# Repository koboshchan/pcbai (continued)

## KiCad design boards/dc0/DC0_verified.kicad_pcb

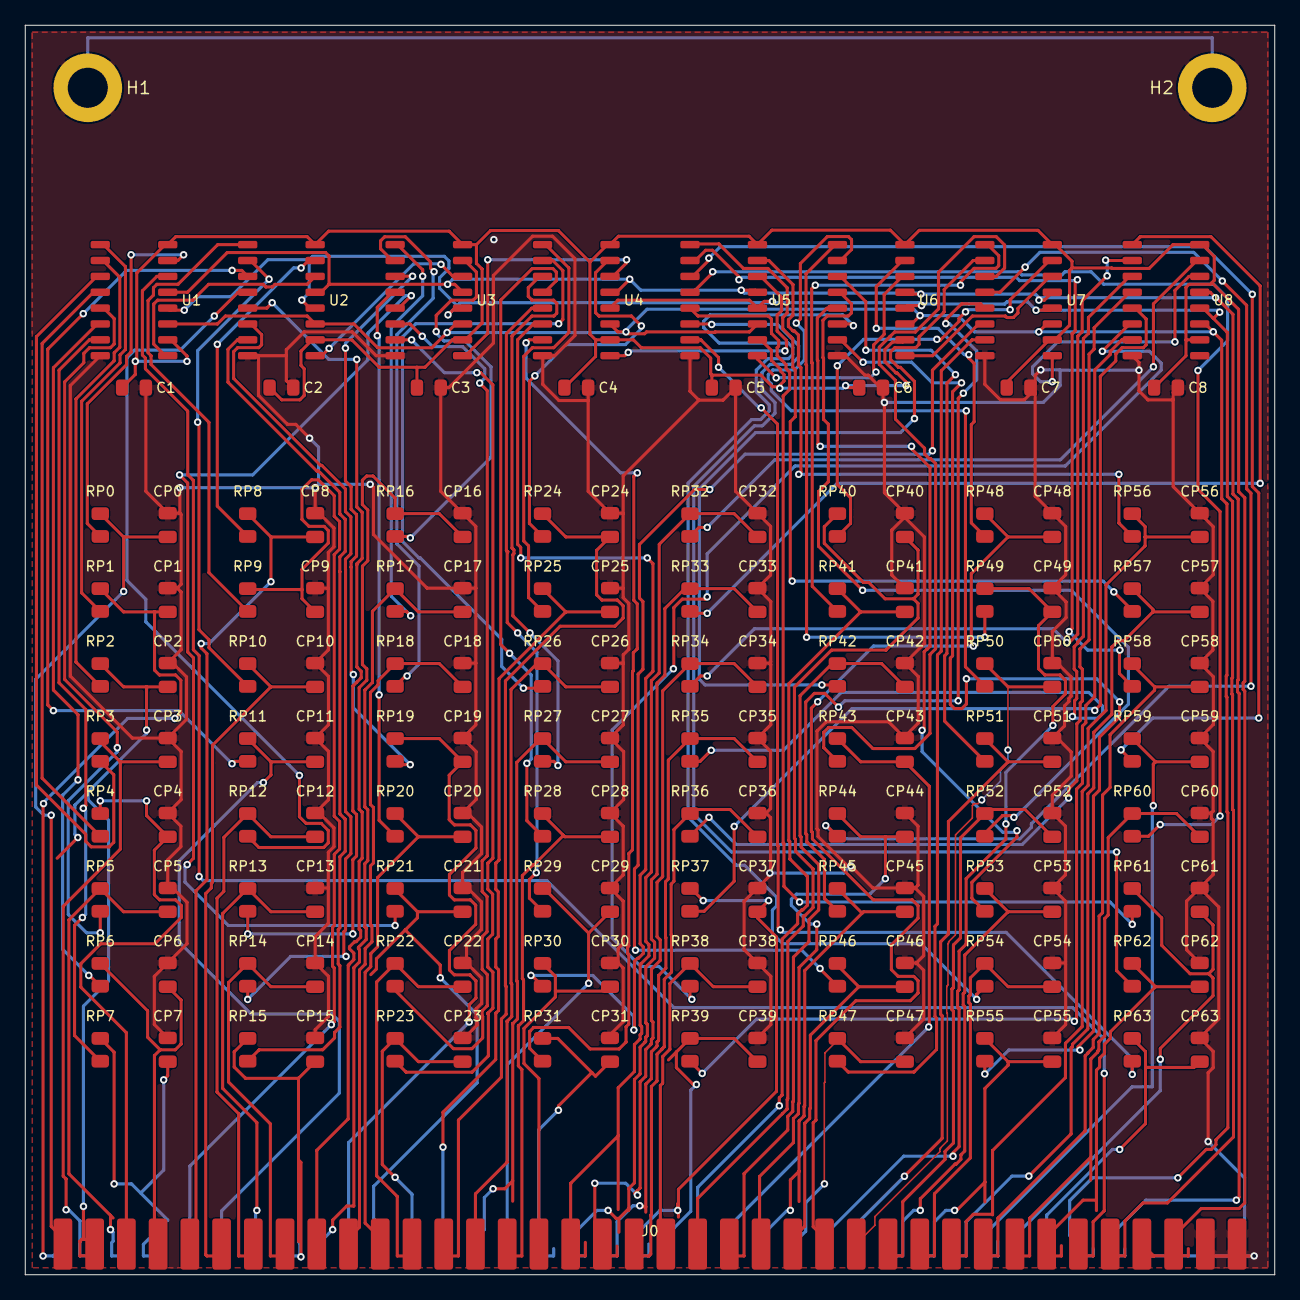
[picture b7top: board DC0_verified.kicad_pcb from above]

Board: 2 copper layers, 100.0 x 100.0 mm, 147 parts (0 on the bottom side), 141 nets.

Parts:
C1, C2, C3, C4, C5, C6, C7, C8: 0.1uF; C_0805_2012Metric
CP0, CP1, CP2, CP3, CP4, CP5, CP6, CP7, CP8, CP9, CP10, CP11, CP12, CP13, CP14, CP15, CP16, CP17, CP18, CP19, CP20, CP21, CP22, CP23, CP24, CP25, CP26, CP27, CP28, CP29, CP30, CP31, CP32, CP33, CP34, CP35, CP36, CP37, CP38, CP39, CP40, CP41, CP42, CP43, CP44, CP45, CP46, CP47, CP48, CP49, CP50, CP51, CP52, CP53, CP54, CP55, CP56, CP57, CP58, CP59, CP60, CP61, CP62, CP63: 1uF; C_0805_2012Metric
H1, H2: MountingHole; MountingHole_3.2mm_M3_Pad
J0: 2x38_2.54mm_GENERIC_MANUAL_STRADDLE; Straddle2x38
RP0, RP1, RP2, RP3, RP4, RP5, RP6, RP7, RP8, RP9, RP10, RP11, RP12, RP13, RP14, RP15, RP16, RP17, RP18, RP19, RP20, RP21, RP22, RP23, RP24, RP25, RP26, RP27, RP28, RP29, RP30, RP31, RP32, RP33, RP34, RP35, RP36, RP37, RP38, RP39, RP40, RP41, RP42, RP43, RP44, RP45, RP46, RP47, RP48, RP49, RP50, RP51, RP52, RP53, RP54, RP55, RP56, RP57, RP58, RP59, RP60, RP61, RP62, RP63: 10k; R_0805_2012Metric
U1, U2, U3, U4, U5, U6, U7, U8: 74AHCT595S16-13; SOIC-16_3.9x9.9mm_P1.27mm

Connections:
+5V: C1.1, C2.1, C3.1, C4.1, C5.1, C6.1, C7.1, C8.1, J0.69, J0.71, U1.10, U1.16, U2.10, U2.16, U3.10, U3.16, U4.10, U4.16, U5.10, U5.16, U6.10, U6.16, U7.10, U7.16, U8.10, U8.16
GND: C1.2, C2.2, C3.2, C4.2, C5.2, C6.2, C7.2, C8.2, CP0.2, CP1.2, CP2.2, CP3.2, CP4.2, CP5.2, CP6.2, CP7.2, CP8.2, CP9.2, CP10.2, CP11.2, CP12.2, CP13.2, CP14.2, CP15.2, CP16.2, CP17.2, CP18.2, CP19.2, CP20.2, CP21.2, CP22.2, CP23.2, CP24.2, CP25.2, CP26.2, CP27.2, CP28.2, CP29.2, CP30.2, CP31.2, CP32.2, CP33.2, CP34.2, CP35.2, CP36.2, CP37.2, CP38.2, CP39.2, CP40.2, CP41.2, CP42.2, CP43.2, CP44.2, CP45.2, CP46.2, CP47.2, CP48.2, CP49.2, CP50.2, CP51.2, CP52.2, CP53.2, CP54.2, CP55.2, CP56.2, CP57.2, CP58.2, CP59.2, CP60.2, CP61.2, CP62.2, CP63.2, H1.1, H2.1, J0.70, J0.72, J0.73, J0.74, J0.75, J0.76, U1.8, U2.8, U3.8, U4.8, U5.8, U6.8, U7.8, U8.8
IN_0: CP0.1, J0.1, RP0.2
IN_1: CP1.1, J0.2, RP1.2
IN_2: CP2.1, J0.3, RP2.2
IN_3: CP3.1, J0.4, RP3.2
IN_4: CP4.1, J0.5, RP4.2
IN_5: CP5.1, J0.6, RP5.2
IN_6: CP6.1, J0.7, RP6.2
IN_7: CP7.1, J0.8, RP7.2
IN_8: CP8.1, J0.9, RP8.2
IN_9: CP9.1, J0.10, RP9.2
IN_10: CP10.1, J0.11, RP10.2
IN_11: CP11.1, J0.12, RP11.2
IN_12: CP12.1, J0.13, RP12.2
IN_13: CP13.1, J0.14, RP13.2
IN_14: CP14.1, J0.15, RP14.2
IN_15: CP15.1, J0.16, RP15.2
IN_16: CP16.1, J0.17, RP16.2
IN_17: CP17.1, J0.18, RP17.2
IN_18: CP18.1, J0.19, RP18.2
IN_19: CP19.1, J0.20, RP19.2
IN_20: CP20.1, J0.21, RP20.2
IN_21: CP21.1, J0.22, RP21.2
IN_22: CP22.1, J0.23, RP22.2
IN_23: CP23.1, J0.24, RP23.2
IN_24: CP24.1, J0.25, RP24.2
IN_25: CP25.1, J0.26, RP25.2
IN_26: CP26.1, J0.27, RP26.2
IN_27: CP27.1, J0.28, RP27.2
IN_28: CP28.1, J0.29, RP28.2
IN_29: CP29.1, J0.30, RP29.2
IN_30: CP30.1, J0.31, RP30.2
IN_31: CP31.1, J0.32, RP31.2
IN_32: CP32.1, J0.33, RP32.2
IN_33: CP33.1, J0.34, RP33.2
IN_34: CP34.1, J0.35, RP34.2
IN_35: CP35.1, J0.36, RP35.2
IN_36: CP36.1, J0.37, RP36.2
IN_37: CP37.1, J0.38, RP37.2
IN_38: CP38.1, J0.39, RP38.2
IN_39: CP39.1, J0.40, RP39.2
IN_40: CP40.1, J0.41, RP40.2
IN_41: CP41.1, J0.42, RP41.2
IN_42: CP42.1, J0.43, RP42.2
IN_43: CP43.1, J0.44, RP43.2
IN_44: CP44.1, J0.45, RP44.2
IN_45: CP45.1, J0.46, RP45.2
IN_46: CP46.1, J0.47, RP46.2
IN_47: CP47.1, J0.48, RP47.2
IN_48: CP48.1, J0.49, RP48.2
IN_49: CP49.1, J0.50, RP49.2
IN_50: CP50.1, J0.51, RP50.2
IN_51: CP51.1, J0.52, RP51.2
IN_52: CP52.1, J0.53, RP52.2
IN_53: CP53.1, J0.54, RP53.2
IN_54: CP54.1, J0.55, RP54.2
IN_55: CP55.1, J0.56, RP55.2
IN_56: CP56.1, J0.57, RP56.2
IN_57: CP57.1, J0.58, RP57.2
IN_58: CP58.1, J0.59, RP58.2
IN_59: CP59.1, J0.60, RP59.2
IN_60: CP60.1, J0.61, RP60.2
IN_61: CP61.1, J0.62, RP61.2
IN_62: CP62.1, J0.63, RP62.2
IN_63: CP63.1, J0.64, RP63.2
RAW_IN_0: RP0.1, U1.15
RAW_IN_1: RP1.1, U1.1
RAW_IN_2: RP2.1, U1.2
RAW_IN_3: RP3.1, U1.3
RAW_IN_4: RP4.1, U1.4
RAW_IN_5: RP5.1, U1.5
RAW_IN_6: RP6.1, U1.6
RAW_IN_7: RP7.1, U1.7
RAW_IN_8: RP8.1, U2.15
RAW_IN_9: RP9.1, U2.1
RAW_IN_10: RP10.1, U2.2
RAW_IN_11: RP11.1, U2.3
RAW_IN_12: RP12.1, U2.4
RAW_IN_13: RP13.1, U2.5
RAW_IN_14: RP14.1, U2.6
RAW_IN_15: RP15.1, U2.7
RAW_IN_16: RP16.1, U3.15
RAW_IN_17: RP17.1, U3.1
RAW_IN_18: RP18.1, U3.2
RAW_IN_19: RP19.1, U3.3
RAW_IN_20: RP20.1, U3.4
RAW_IN_21: RP21.1, U3.5
RAW_IN_22: RP22.1, U3.6
RAW_IN_23: RP23.1, U3.7
RAW_IN_24: RP24.1, U4.15
RAW_IN_25: RP25.1, U4.1
RAW_IN_26: RP26.1, U4.2
RAW_IN_27: RP27.1, U4.3
RAW_IN_28: RP28.1, U4.4
RAW_IN_29: RP29.1, U4.5
RAW_IN_30: RP30.1, U4.6
RAW_IN_31: RP31.1, U4.7
RAW_IN_32: RP32.1, U8.15
RAW_IN_33: RP33.1, U8.1
RAW_IN_34: RP34.1, U8.2
RAW_IN_35: RP35.1, U8.3
RAW_IN_36: RP36.1, U8.4
RAW_IN_37: RP37.1, U8.5
RAW_IN_38: RP38.1, U8.6
RAW_IN_39: RP39.1, U8.7
RAW_IN_40: RP40.1, U7.15
RAW_IN_41: RP41.1, U7.1
RAW_IN_42: RP42.1, U7.2
RAW_IN_43: RP43.1, U7.3
RAW_IN_44: RP44.1, U7.4
RAW_IN_45: RP45.1, U7.5
RAW_IN_46: RP46.1, U7.6
RAW_IN_47: RP47.1, U7.7
RAW_IN_48: RP48.1, U6.15
RAW_IN_49: RP49.1, U6.1
RAW_IN_50: RP50.1, U6.2
RAW_IN_51: RP51.1, U6.3
RAW_IN_52: RP52.1, U6.4
RAW_IN_53: RP53.1, U6.5
RAW_IN_54: RP54.1, U6.6
RAW_IN_55: RP55.1, U6.7
RAW_IN_56: RP56.1, U5.15
RAW_IN_57: RP57.1, U5.1
RAW_IN_58: RP58.1, U5.2
RAW_IN_59: RP59.1, U5.3
RAW_IN_60: RP60.1, U5.4
RAW_IN_61: RP61.1, U5.5
RAW_IN_62: RP62.1, U5.6
RAW_IN_63: RP63.1, U5.7
SPI_LATCH: J0.67, U1.12, U2.12, U3.12, U4.12, U5.12, U6.12, U7.12, U8.12
SPI_MOSI: J0.65, U1.14
SPI_OE: J0.68, U1.13, U2.13, U3.13, U4.13, U5.13, U6.13, U7.13, U8.13
SPI_SCK: J0.66, U1.11, U2.11, U3.11, U4.11, U5.11, U6.11, U7.11, U8.11
SR_CHAIN_1: U1.9, U2.14
SR_CHAIN_2: U2.9, U3.14
SR_CHAIN_3: U3.9, U4.14
SR_CHAIN_4: U4.9, U5.14
SR_CHAIN_5: U5.9, U6.14
SR_CHAIN_6: U6.9, U7.14
SR_CHAIN_7: U7.9, U8.14

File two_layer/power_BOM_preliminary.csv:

Comment,Designator,Footprint,LCSC Part #
Diodes 74AHCT595S16-13 - approved JLC Extended SMT assembly all8,"U_SR1,U_SR2,U_SR3,U_SR4,U_SR5,U_SR6,U_SR7,U_SR8",SOIC-16_3.9x9.9mm_P1.27mm,C126402
ST L7805CV - manual TH assembly; cooling optional recommended; clock limits require qualification,U_REG5,TO-220-3_Vertical,C111887
1uF 50V X7R +/-10% Samsung CL21B105KBFNNNE - JLC Basic SMT practical input bypass,C_REG_IN,C_0805_2012Metric,C28323
0.1uF 50V X7R - purchasing part pending,C_REG_OUT,C_0805_2012Metric,
10uF >=16V polarized - purchasing part pending,C_REG_BULK,CP_Elec_5x5.8,
0ohm mandatory shared5V reference link - purchasing part pending,R_REF_LINK,R_0805_2012Metric,
820ohm5% >=0.125W minimum load - purchasing part pending,R_REG_MINLOAD,R_0805_2012Metric,

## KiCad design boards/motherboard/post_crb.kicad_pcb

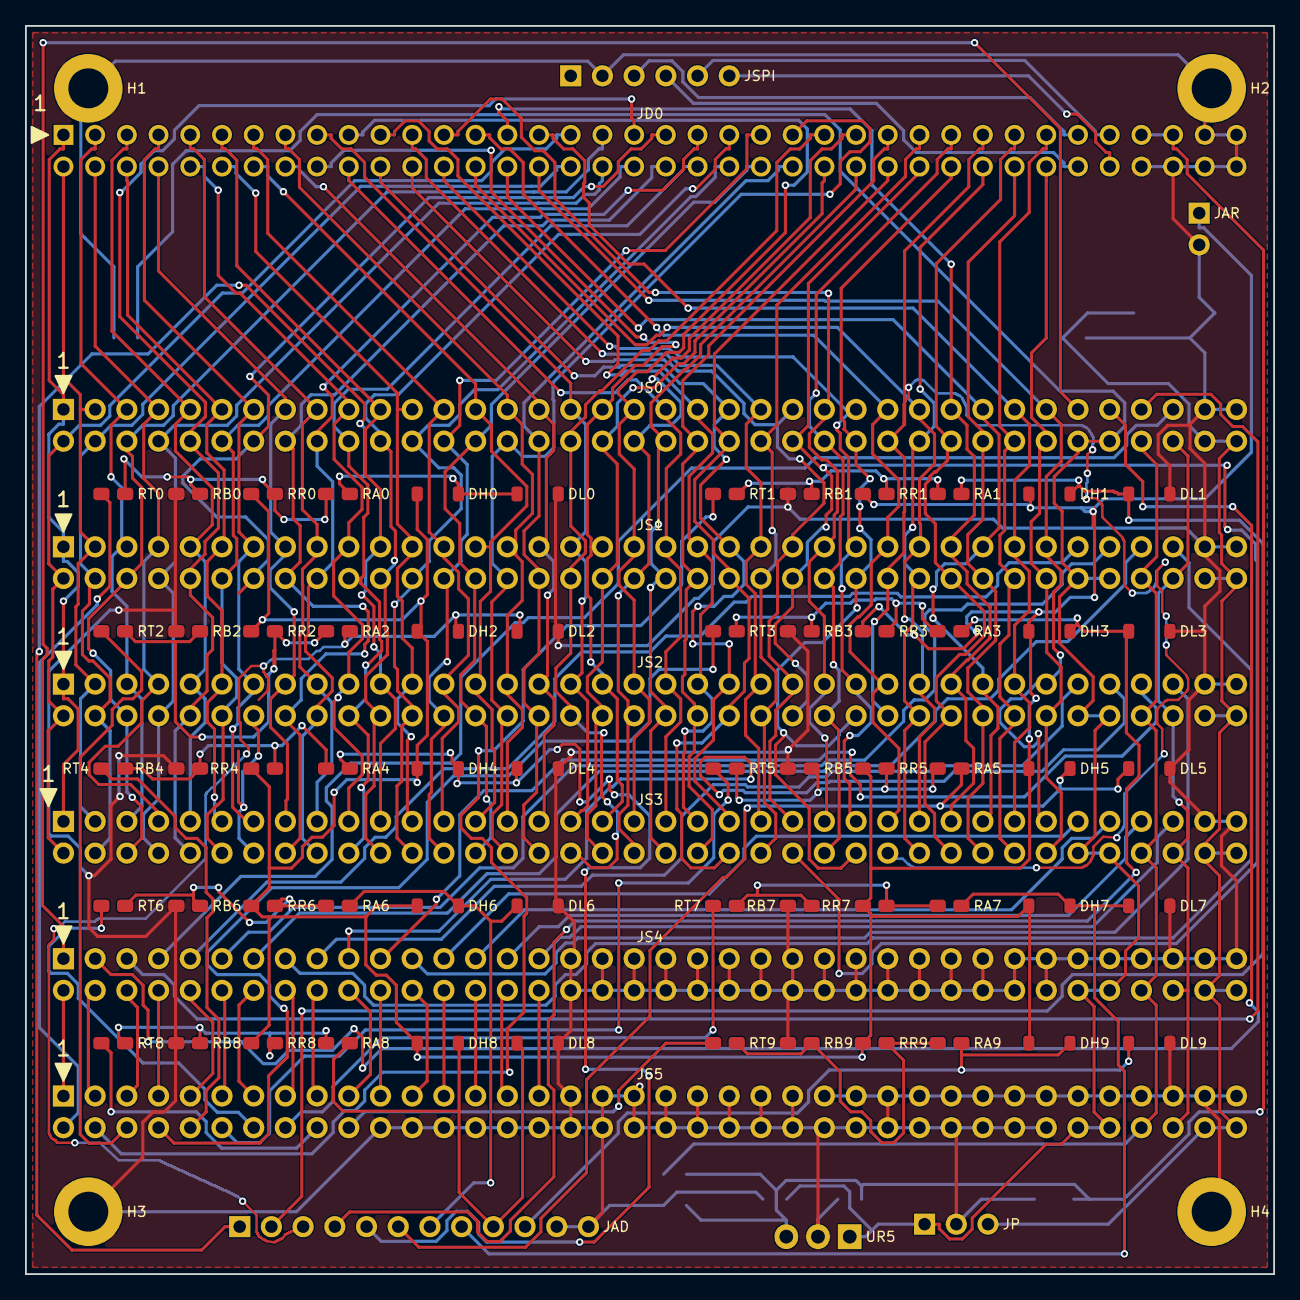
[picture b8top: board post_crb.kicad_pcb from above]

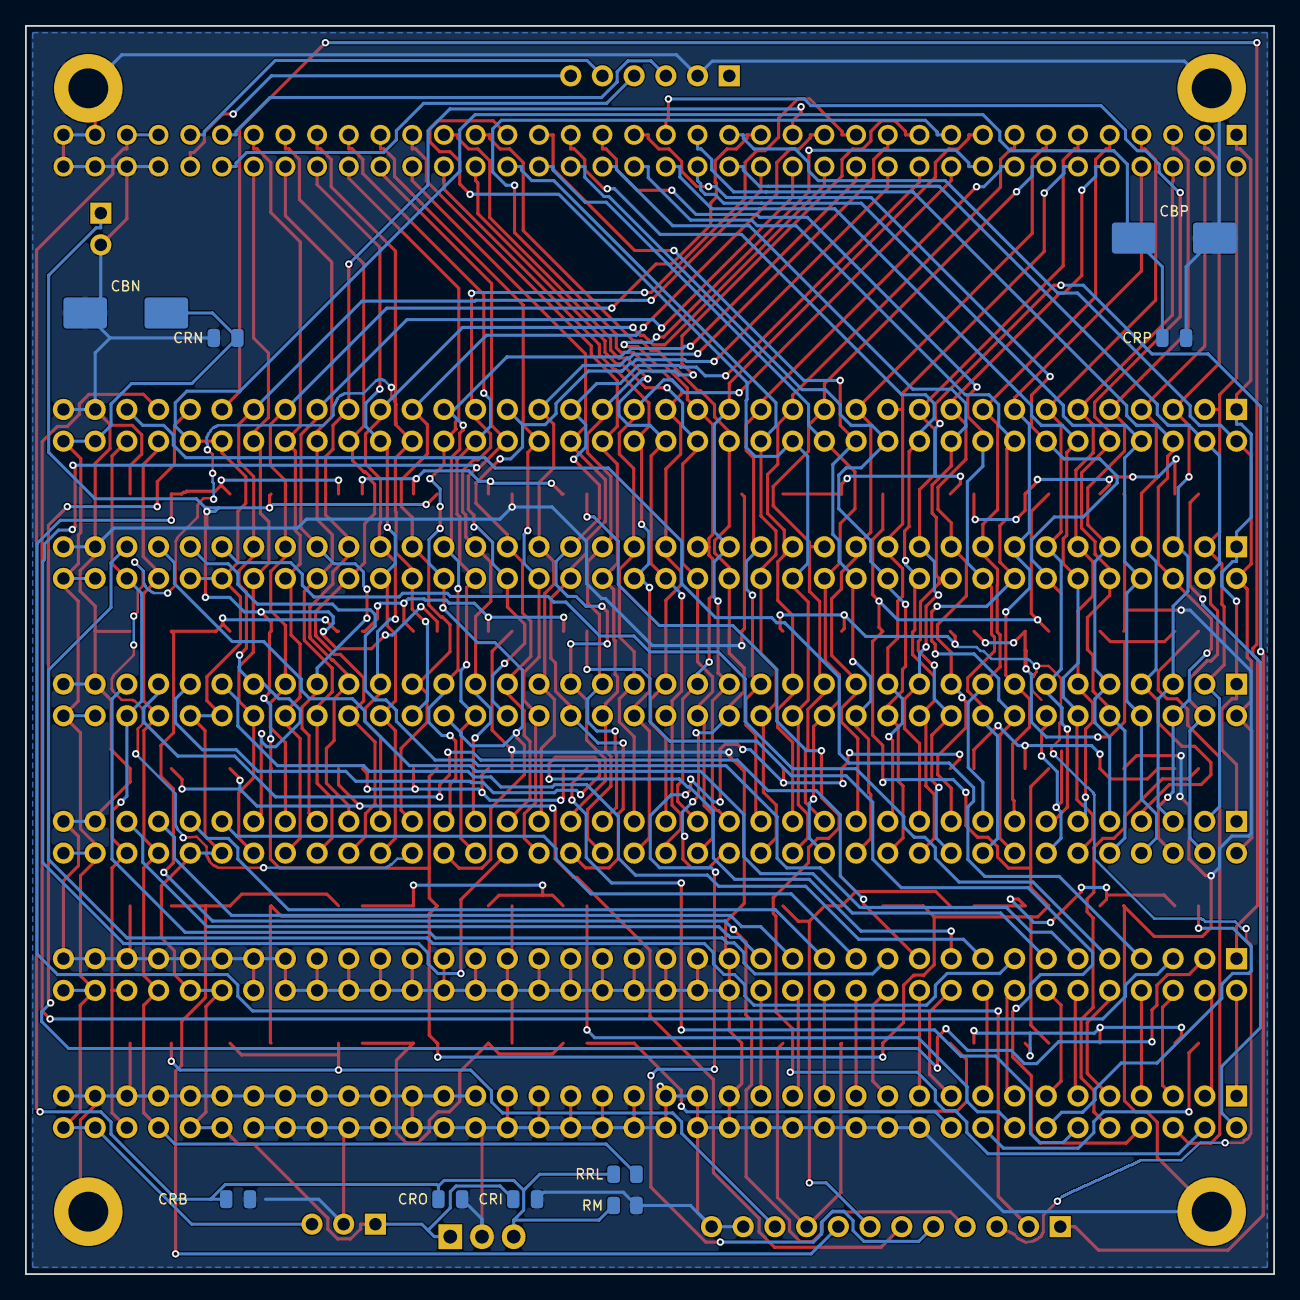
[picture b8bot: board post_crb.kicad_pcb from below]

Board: 2 copper layers, 100.0 x 100.0 mm, 85 parts (9 on the bottom side), 137 nets.

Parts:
CBN: 100uF; CP_Elec_8x10
CBP: 100uF; CP_Elec_8x10
CRB: 10uF; C_0805_2012Metric
CRI: 1uF; C_0805_2012Metric
CRN: 0.1uF; C_0805_2012Metric
CRO: 0.1uF; C_0805_2012Metric
CRP: 0.1uF; C_0805_2012Metric
DH0, DH1, DH2, DH3, DH4, DH5, DH6, DH7, DH8, DH9: 1N4148W; D_SOD-123
DL0, DL1, DL2, DL3, DL4, DL5, DL6, DL7, DL8, DL9: 1N4148W; D_SOD-123
H1, H2, H3, H4: MountingHole; MountingHole_3.2mm_M3_Pad
JAD: Scores_DIV_3V3_Out; PinHeader_1x12_P2.54mm_Vertical
JAR: 3V3_GND_FROM_MCU; PinHeader_1x02_P2.54mm_Vertical
JD0: 2x38_2.54mm_GENERIC_MANUAL_SOCKET; Socket2x38
JP: +15V_GND_-15V; PinHeader_1x03_P2.54mm_Vertical
JS0: Slot0: DC1A (L1 Neurons 0..3); PinSocket_2x38_P2.54mm_Vertical
JS1: Slot1: DC1B (L1 Neurons 4..7); PinSocket_2x38_P2.54mm_Vertical
JS2: Slot2: DC1C (L1 Neurons 8..11); PinSocket_2x38_P2.54mm_Vertical
JS3: Slot3: DC1D (L1 Neurons 12..15); PinSocket_2x38_P2.54mm_Vertical
JS4: Slot4: DC2 (16x Active Precision ReLU); PinSocket_2x38_P2.54mm_Vertical
JS5: Slot5: DC3 (L2 Weights + 10-Way WTA); PinSocket_2x38_P2.54mm_Vertical
JSPI: MCU_3V3_SPI_PIN1_NC; PinHeader_1x06_P2.54mm_Vertical
RA0, RA1, RA2, RA3, RA4, RA5, RA6, RA7, RA8, RA9: 1k; R_0805_2012Metric
RB0, RB1, RB2, RB3, RB4, RB5, RB6, RB7, RB8, RB9: 22k; R_0805_2012Metric
RM: 820; R_0805_2012Metric
RR0, RR1, RR2, RR3, RR4, RR5, RR6, RR7, RR8, RR9: 22k; R_0805_2012Metric
RRL: 0R; R_0805_2012Metric
RT0, RT1, RT2, RT3, RT4, RT5, RT6, RT7, RT8, RT9: 220k; R_0805_2012Metric
UR5: L7805CV; TO-220-3_Vertical

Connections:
+3V3_ADC: DH0.1, DH1.1, DH2.1, DH3.1, DH4.1, DH5.1, DH6.1, DH7.1, DH8.1, DH9.1, JAR.1, RR0.1, RR1.1, RR2.1, RR3.1, RR4.1, RR5.1, RR6.1, RR7.1, RR8.1, RR9.1
+5V: CRB.1, CRO.1, JD0.69, JD0.71, RM.1, RRL.1, UR5.3
+5V_REF: JS0.B35, JS1.B35, JS2.B35, JS3.B35, JS4.B35, JS5.B35, RRL.2
+15V: CBP.1, CRI.1, CRP.1, JP.1, JS0.B33, JS0.B34, JS1.B33, JS1.B34, JS2.B33, JS2.B34, JS3.B33, JS3.B34, JS4.B33, JS4.B34, JS5.B33, JS5.B34, UR5.1
-5V_REF: JS0.B36, JS1.B36, JS2.B36, JS3.B36, JS4.B36, JS5.B36
-15V: CBN.2, CRN.2, JP.3, JS0.B37, JS0.B38, JS1.B37, JS1.B38, JS2.B37, JS2.B38, JS3.B37, JS3.B38, JS4.B37, JS4.B38, JS5.B37, JS5.B38
ACT_0: JS4.B1, JS5.A1
ACT_1: JS4.B2, JS5.A2
ACT_2: JS4.B3, JS5.A3
ACT_3: JS4.B4, JS5.A4
ACT_4: JS4.B5, JS5.A5
ACT_5: JS4.B6, JS5.A6
ACT_6: JS4.B7, JS5.A7
ACT_7: JS4.B8, JS5.A8
ACT_8: JS4.B9, JS5.A9
ACT_9: JS4.B10, JS5.A10
ACT_10: JS4.B11, JS5.A11
ACT_11: JS4.B12, JS5.A12
ACT_12: JS4.B13, JS5.A13
ACT_13: JS4.B14, JS5.A14
ACT_14: JS4.B15, JS5.A15
ACT_15: JS4.B16, JS5.A16
ADC_0: DH0.2, DL0.1, JAD.1, RA0.2
ADC_1: DH1.2, DL1.1, JAD.2, RA1.2
ADC_2: DH2.2, DL2.1, JAD.3, RA2.2
ADC_3: DH3.2, DL3.1, JAD.4, RA3.2
ADC_4: DH4.2, DL4.1, JAD.5, RA4.2
ADC_5: DH5.2, DL5.1, JAD.6, RA5.2
ADC_6: DH6.2, DL6.1, JAD.7, RA6.2
ADC_7: DH7.2, DL7.1, JAD.8, RA7.2
ADC_8: DH8.2, DL8.1, JAD.9, RA8.2
ADC_9: DH9.2, DL9.1, JAD.10, RA9.2
GND: CBN.1, CBP.2, CRB.2, CRI.2, CRN.1, CRO.2, CRP.2, DL0.2, DL1.2, DL2.2, DL3.2, DL4.2, DL5.2, DL6.2, DL7.2, DL8.2, DL9.2, H1.1, H2.1, H3.1, H4.1, JAD.11, JAD.12, JAR.2, JD0.70, JD0.72, JD0.73, JD0.74, JD0.75, JD0.76, JP.2, JS0.A37, JS0.A38, JS1.A37, JS1.A38, JS2.A37, JS2.A38, JS3.A37, JS3.A38, JS4.A17, JS4.A18, JS4.A19, JS4.A20, JS4.A21, JS4.A22, JS4.A23, JS4.A24, JS4.A25, JS4.A26, JS4.A27, JS4.A28, JS4.A29, JS4.A30, JS4.A31, JS4.A32, JS4.A33, JS4.A34, JS4.A35, JS4.A36, JS4.A37, JS4.A38, JS4.B17, JS4.B18, JS4.B19, JS4.B20, JS4.B21, JS4.B22, JS4.B23, JS4.B24, JS4.B25, JS4.B26, JS4.B27, JS4.B28, JS4.B29, JS4.B30, JS4.B31, JS4.B32, JS5.A17, JS5.A18, JS5.A19, JS5.A20, JS5.A21, JS5.A22, JS5.A23, JS5.A24, JS5.A25, JS5.A26, JS5.A27, JS5.A28, JS5.A29, JS5.A30, JS5.A31, JS5.A32, JS5.A33, JS5.A34, JS5.A35, JS5.A36, JS5.A37, JS5.A38, JS5.B11, JS5.B12, JS5.B13, JS5.B14, JS5.B15, JS5.B16, JS5.B17, JS5.B18, JS5.B19, JS5.B20, JS5.B21, JS5.B22, JS5.B23, JS5.B24, JS5.B25, JS5.B26, JS5.B27, JS5.B28, JS5.B29, JS5.B30, JS5.B31, JS5.B32, JSPI.2, RB0.1, RB1.1, RB2.1, RB3.1, RB4.1, RB5.1, RB6.1, RB7.1, RB8.1, RB9.1, RM.2, UR5.2
IN_0: JD0.1, JS0.A1, JS1.A1, JS2.A1, JS3.A1
IN_1: JD0.2, JS0.A2, JS1.A2, JS2.A2, JS3.A2
IN_2: JD0.3, JS0.A3, JS1.A3, JS2.A3, JS3.A3
IN_3: JD0.4, JS0.A4, JS1.A4, JS2.A4, JS3.A4
IN_4: JD0.5, JS0.A5, JS1.A5, JS2.A5, JS3.A5
IN_5: JD0.6, JS0.A6, JS1.A6, JS2.A6, JS3.A6
IN_6: JD0.7, JS0.A7, JS1.A7, JS2.A7, JS3.A7
IN_7: JD0.8, JS0.A8, JS1.A8, JS2.A8, JS3.A8
IN_8: JD0.9, JS0.A9, JS1.A9, JS2.A9, JS3.A9
IN_9: JD0.10, JS0.A10, JS1.A10, JS2.A10, JS3.A10
IN_10: JD0.11, JS0.A11, JS1.A11, JS2.A11, JS3.A11
IN_11: JD0.12, JS0.A12, JS1.A12, JS2.A12, JS3.A12
IN_12: JD0.13, JS0.A13, JS1.A13, JS2.A13, JS3.A13
IN_13: JD0.14, JS0.A14, JS1.A14, JS2.A14, JS3.A14
IN_14: JD0.15, JS0.A15, JS1.A15, JS2.A15, JS3.A15
IN_15: JD0.16, JS0.A16, JS1.A16, JS2.A16, JS3.A16
IN_16: JD0.17, JS0.A17, JS1.A17, JS2.A17, JS3.A17
IN_17: JD0.18, JS0.A18, JS1.A18, JS2.A18, JS3.A18
IN_18: JD0.19, JS0.A19, JS1.A19, JS2.A19, JS3.A19
IN_19: JD0.20, JS0.A20, JS1.A20, JS2.A20, JS3.A20
IN_20: JD0.21, JS0.A21, JS1.A21, JS2.A21, JS3.A21
IN_21: JD0.22, JS0.A22, JS1.A22, JS2.A22, JS3.A22
IN_22: JD0.23, JS0.A23, JS1.A23, JS2.A23, JS3.A23
IN_23: JD0.24, JS0.A24, JS1.A24, JS2.A24, JS3.A24
IN_24: JD0.25, JS0.A25, JS1.A25, JS2.A25, JS3.A25
IN_25: JD0.26, JS0.A26, JS1.A26, JS2.A26, JS3.A26
IN_26: JD0.27, JS0.A27, JS1.A27, JS2.A27, JS3.A27
IN_27: JD0.28, JS0.A28, JS1.A28, JS2.A28, JS3.A28
IN_28: JD0.29, JS0.A29, JS1.A29, JS2.A29, JS3.A29
IN_29: JD0.30, JS0.A30, JS1.A30, JS2.A30, JS3.A30
IN_30: JD0.31, JS0.A31, JS1.A31, JS2.A31, JS3.A31
IN_31: JD0.32, JS0.A32, JS1.A32, JS2.A32, JS3.A32
IN_32: JD0.33, JS0.B1, JS1.B1, JS2.B1, JS3.B1
IN_33: JD0.34, JS0.B2, JS1.B2, JS2.B2, JS3.B2
IN_34: JD0.35, JS0.B3, JS1.B3, JS2.B3, JS3.B3
IN_35: JD0.36, JS0.B4, JS1.B4, JS2.B4, JS3.B4
IN_36: JD0.37, JS0.B5, JS1.B5, JS2.B5, JS3.B5
IN_37: JD0.38, JS0.B6, JS1.B6, JS2.B6, JS3.B6
IN_38: JD0.39, JS0.B7, JS1.B7, JS2.B7, JS3.B7
IN_39: JD0.40, JS0.B8, JS1.B8, JS2.B8, JS3.B8
IN_40: JD0.41, JS0.B9, JS1.B9, JS2.B9, JS3.B9
IN_41: JD0.42, JS0.B10, JS1.B10, JS2.B10, JS3.B10
IN_42: JD0.43, JS0.B11, JS1.B11, JS2.B11, JS3.B11
IN_43: JD0.44, JS0.B12, JS1.B12, JS2.B12, JS3.B12
IN_44: JD0.45, JS0.B13, JS1.B13, JS2.B13, JS3.B13
IN_45: JD0.46, JS0.B14, JS1.B14, JS2.B14, JS3.B14
IN_46: JD0.47, JS0.B15, JS1.B15, JS2.B15, JS3.B15
IN_47: JD0.48, JS0.B16, JS1.B16, JS2.B16, JS3.B16
IN_48: JD0.49, JS0.B17, JS1.B17, JS2.B17, JS3.B17
IN_49: JD0.50, JS0.B18, JS1.B18, JS2.B18, JS3.B18
IN_50: JD0.51, JS0.B19, JS1.B19, JS2.B19, JS3.B19
IN_51: JD0.52, JS0.B20, JS1.B20, JS2.B20, JS3.B20
IN_52: JD0.53, JS0.B21, JS1.B21, JS2.B21, JS3.B21
IN_53: JD0.54, JS0.B22, JS1.B22, JS2.B22, JS3.B22
IN_54: JD0.55, JS0.B23, JS1.B23, JS2.B23, JS3.B23
IN_55: JD0.56, JS0.B24, JS1.B24, JS2.B24, JS3.B24
IN_56: JD0.57, JS0.B25, JS1.B25, JS2.B25, JS3.B25
IN_57: JD0.58, JS0.B26, JS1.B26, JS2.B26, JS3.B26
IN_58: JD0.59, JS0.B27, JS1.B27, JS2.B27, JS3.B27
IN_59: JD0.60, JS0.B28, JS1.B28, JS2.B28, JS3.B28
IN_60: JD0.61, JS0.B29, JS1.B29, JS2.B29, JS3.B29
IN_61: JD0.62, JS0.B30, JS1.B30, JS2.B30, JS3.B30
IN_62: JD0.63, JS0.B31, JS1.B31, JS2.B31, JS3.B31
IN_63: JD0.64, JS0.B32, JS1.B32, JS2.B32, JS3.B32
SCORE_0: JS5.B1, RT0.1
SCORE_1: JS5.B2, RT1.1
SCORE_2: JS5.B3, RT2.1
SCORE_3: JS5.B4, RT3.1
SCORE_4: JS5.B5, RT4.1
SCORE_5: JS5.B6, RT5.1
SCORE_6: JS5.B7, RT6.1
SCORE_7: JS5.B8, RT7.1
SCORE_8: JS5.B9, RT8.1
SCORE_9: JS5.B10, RT9.1
SCORE_DIV_0: RA0.1, RB0.2, RR0.2, RT0.2
SCORE_DIV_1: RA1.1, RB1.2, RR1.2, RT1.2
SCORE_DIV_2: RA2.1, RB2.2, RR2.2, RT2.2
SCORE_DIV_3: RA3.1, RB3.2, RR3.2, RT3.2
SCORE_DIV_4: RA4.1, RB4.2, RR4.2, RT4.2
SCORE_DIV_5: RA5.1, RB5.2, RR5.2, RT5.2
SCORE_DIV_6: RA6.1, RB6.2, RR6.2, RT6.2
SCORE_DIV_7: RA7.1, RB7.2, RR7.2, RT7.2
SCORE_DIV_8: RA8.1, RB8.2, RR8.2, RT8.2
SCORE_DIV_9: RA9.1, RB9.2, RR9.2, RT9.2
SPI_LATCH: JD0.67, JSPI.5
SPI_MOSI: JD0.65, JSPI.3
SPI_OE: JD0.68, JSPI.6
SPI_SCK: JD0.66, JSPI.4
V_SUM_0: JS0.A33, JS4.A1
V_SUM_1: JS0.A34, JS4.A2
V_SUM_2: JS0.A35, JS4.A3
V_SUM_3: JS0.A36, JS4.A4
V_SUM_4: JS1.A33, JS4.A5
V_SUM_5: JS1.A34, JS4.A6
V_SUM_6: JS1.A35, JS4.A7
V_SUM_7: JS1.A36, JS4.A8
V_SUM_8: JS2.A33, JS4.A9
V_SUM_9: JS2.A34, JS4.A10
V_SUM_10: JS2.A35, JS4.A11
V_SUM_11: JS2.A36, JS4.A12
V_SUM_12: JS3.A33, JS4.A13
V_SUM_13: JS3.A34, JS4.A14
V_SUM_14: JS3.A35, JS4.A15
V_SUM_15: JS3.A36, JS4.A16

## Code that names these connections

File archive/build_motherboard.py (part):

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        slots_pcb.append(fp_socket_2x20(f"J_SLOT{slot_idx}_B", f"Slot{slot_idx}_B", 50.0, yb, 90, sock_b_nets))

    # External Connectors:
    # J_PIXELS_A at (12.0, 50.0), rot 0: Pins 1..32 = IN_0..IN_31, Pins 33..40 = GND
    j_pix_a_nets = {str(p+1): (net_map[f"IN_{p}"], f"IN_{p}") for p in range(32)}
    for p in range(33, 41): j_pix_a_nets[str(p)] = (net_map["GND"], "GND")
    j_pix_a = fp_header_2x20("J_PIXELS_A", "Pixels_0_31_In", 12.0, 50.0, 0, j_pix_a_nets)

    # J_PIXELS_B at (88.0, 50.0), rot 0: Pins 1..32 = IN_32..IN_63, Pins 33..40 = GND
    j_pix_b_nets = {str(p+1): (net_map[f"IN_{32+p}"], f"IN_{32+p}") for p in range(32)}
    for p in range(33, 41): j_pix_b_nets[str(p)] = (net_map["GND"], "GND")
    j_pix_b = fp_header_2x20("J_PIXELS_B", "Pixels_32_63_In", 88.0, 50.0, 0, j_pix_b_nets)
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    }
    j_pwr = fp_header_2x05("J_PWR_IN", "Main_Power_In", 12.0, 10.0, 0, j_pwr_nets)

    # J_OUT_SCORES at (88.0, 90.0), rot 0: Pins 1..10 = SCORE_0..9
    j_out_nets = {str(k+1): (net_map[f"SCORE_{k}"], f"SCORE_{k}") for k in range(10)}
    j_out = fp_header_2x05("J_OUT_SCORES", "L2_Scores_Out", 88.0, 90.0, 0, j_out_nets)

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
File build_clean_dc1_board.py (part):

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    # 6. Outputs V_SUM_j to J_BOT pins 33..36:
    # J_BOT pins 33, 34, 35, 36 are at X = 88.28, 90.82, 93.36, 95.90, Y = 115.0
    # From U1 and U2 V_SUM pins, route to J_BOT:
    # V_SUM_0 is at (29.5, 63.525) -> J_BOT pin 33 (88.28, 115.0)
    add_jumper(29.5, 64.0, 88.28, 112.0, f"V_SUM_{n0}")
    add_track(29.5, 63.525, 29.5, 64.0, f"V_SUM_{n0}")
    add_track(88.28, 112.0, 88.28, 115.0, f"V_SUM_{n0}")

    # V_SUM_1 is at (40.5, 63.525) -> J_BOT pin 34 (90.82, 115.0)
    add_jumper(40.5, 64.0, 90.82, 112.0, f"V_SUM_{n1}")
    add_track(40.5, 63.525, 40.5, 64.0, f"V_SUM_{n1}")
    add_track(90.82, 112.0, 90.82, 115.0, f"V_SUM_{n1}")

    # V_SUM_2 is at (59.5, 63.525) -> J_BOT pin 35 (93.36, 115.0)
    add_jumper(59.5, 64.0, 93.36, 112.0, f"V_SUM_{n2}")
    add_track(59.5, 63.525, 59.5, 64.0, f"V_SUM_{n2}")
    add_track(93.36, 112.0, 93.36, 115.0, f"V_SUM_{n2}")

    # V_SUM_3 is at (70.5, 63.525) -> J_BOT pin 36 (95.90, 115.0)
    add_jumper(70.5, 64.0, 95.90, 112.0, f"V_SUM_{n3}")
    add_track(70.5, 63.525, 70.5, 64.0, f"V_SUM_{n3}")
    add_track(95.90, 112.0, 95.90, 115.0, f"V_SUM_{n3}")
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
